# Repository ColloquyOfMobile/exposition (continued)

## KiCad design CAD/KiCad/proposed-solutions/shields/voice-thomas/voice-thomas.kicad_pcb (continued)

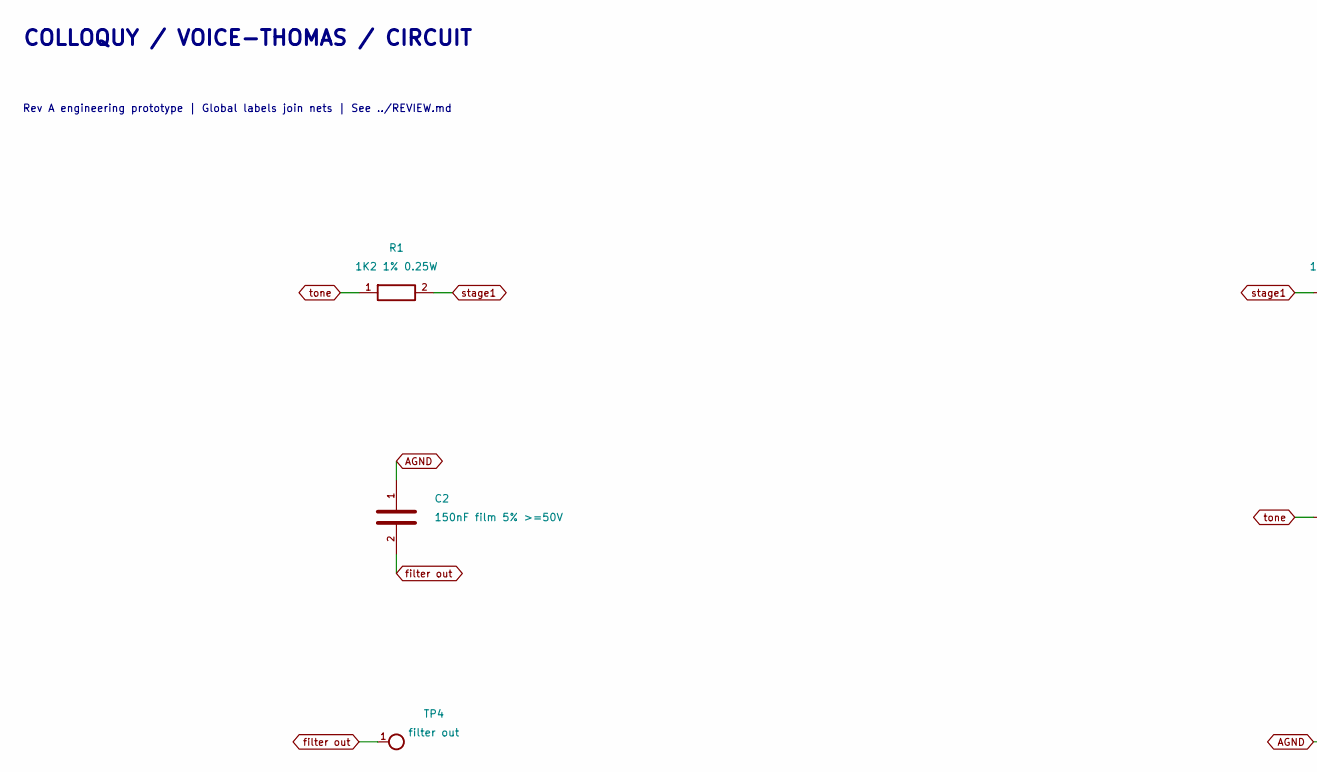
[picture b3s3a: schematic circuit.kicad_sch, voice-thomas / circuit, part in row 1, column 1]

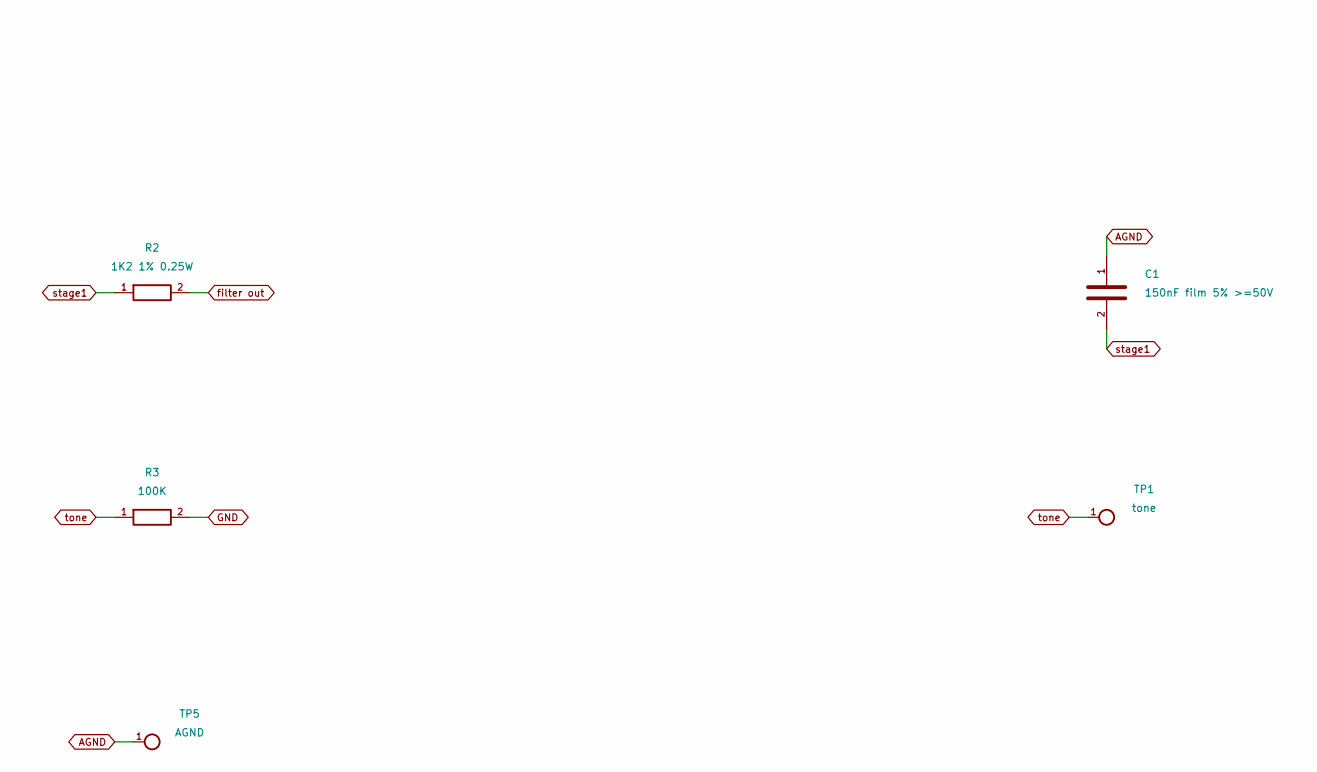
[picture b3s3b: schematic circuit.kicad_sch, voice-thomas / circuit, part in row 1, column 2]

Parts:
C1, C2: 150nF film 5% >=50V; C_Rect_L7.0mm_W6.5mm_P5.00mm
R1, R2: 1K2 1% 0.25W; R_Axial_DIN0207_L6.3mm_D2.5mm_P7.62mm_Horizontal
R3: 100K; R_Axial_DIN0207_L6.3mm_D2.5mm_P7.62mm_Horizontal
TP1: tone; TestPoint_Pad_D1.5mm
TP4: filter out; TestPin_1x01_P2.54mm
TP5: AGND; TestPin_1x01_P2.54mm

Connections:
AGND: C1.1, C2.1, TP5.1; also elsewhere on the board
GND: R3.2; also elsewhere on the board
filter out: C2.2, R2.2, TP4.1; also elsewhere on the board
stage1: C1.2, R1.2, R2.1
tone: R1.1, R3.1, TP1.1; also elsewhere on the board

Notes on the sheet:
COLLOQUY / VOICE-THOMAS / CIRCUIT
Rev A engineering prototype | Global labels join nets | See ../REVIEW.md

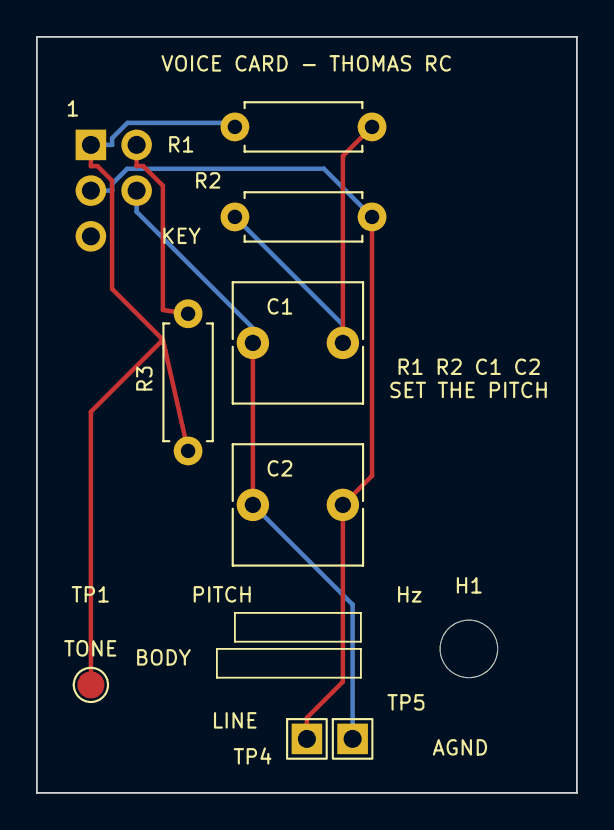
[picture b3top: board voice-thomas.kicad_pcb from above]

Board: 2 copper layers, 30.0 x 42.0 mm, 10 parts (1 on the bottom side), 5 nets.

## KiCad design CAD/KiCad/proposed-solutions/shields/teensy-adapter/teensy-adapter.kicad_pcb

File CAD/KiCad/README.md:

# Electronics: designs, references and production

Use these four folders to distinguish the files' purpose:

| Folder | Contents |
| --- | --- |
| [proposed-solutions](proposed-solutions/) | Editable replacement designs, including selected boards and alternative designs. |
| [old-reference](old-reference/) | Original installation boards, superseded designs and historical exports. |
| [provided-elements](provided-elements/) | Reference models and footprints of purchased/provided modules and component datasheets. |
| [production](production/) | Current checked fabrication, JLCPCB assembly files, schematic SVGs and 45° PCB previews. |

The authoritative manufacture selection is `export_gerbers.py` at the repository root;
`production/manifest.json` records its exact source files and hashes. The server reads
this selection and refuses stale packages. Alternative designs are not manufacturing orders.

| Manufacture | Quantity |
| --- | ---: |
| Shields backplane | 1 |
| Teensy 4.1 adapter | 1 |
| Voice Thomas card | 5 |
| Analyser carrier | 1 |
| **Microphone flex holder, Rev C (32 × 62 mm)** | **6** |
| Female base v2 | 3 |
| Male static v2 | 2 |

The Rev B microphone holder is historical. Manufacture the Rev C **microphone-flex**
board with removable JP1/JP2 selectors and three alternative module orientations.
Fit one MAX9814 module per holder; see its README for initial selector settings and fit checks.

Order packages are under `production/assembly/<board>/`; the combined download is
`production/assembly/colloquy-production.zip`. Each board package contains `gerbers.zip`,
`BOM.csv` with exact manufacturer/LCSC identification, `CPL.csv`, and manual/DNP instructions.
The analyser carrier has no SMD population and is assembled by hand.

Regenerate from the repository root using KiCad's Python: `python export_jlcpcb.py`.
This checks DRC, produces the assembly packages, and refreshes browser assets.

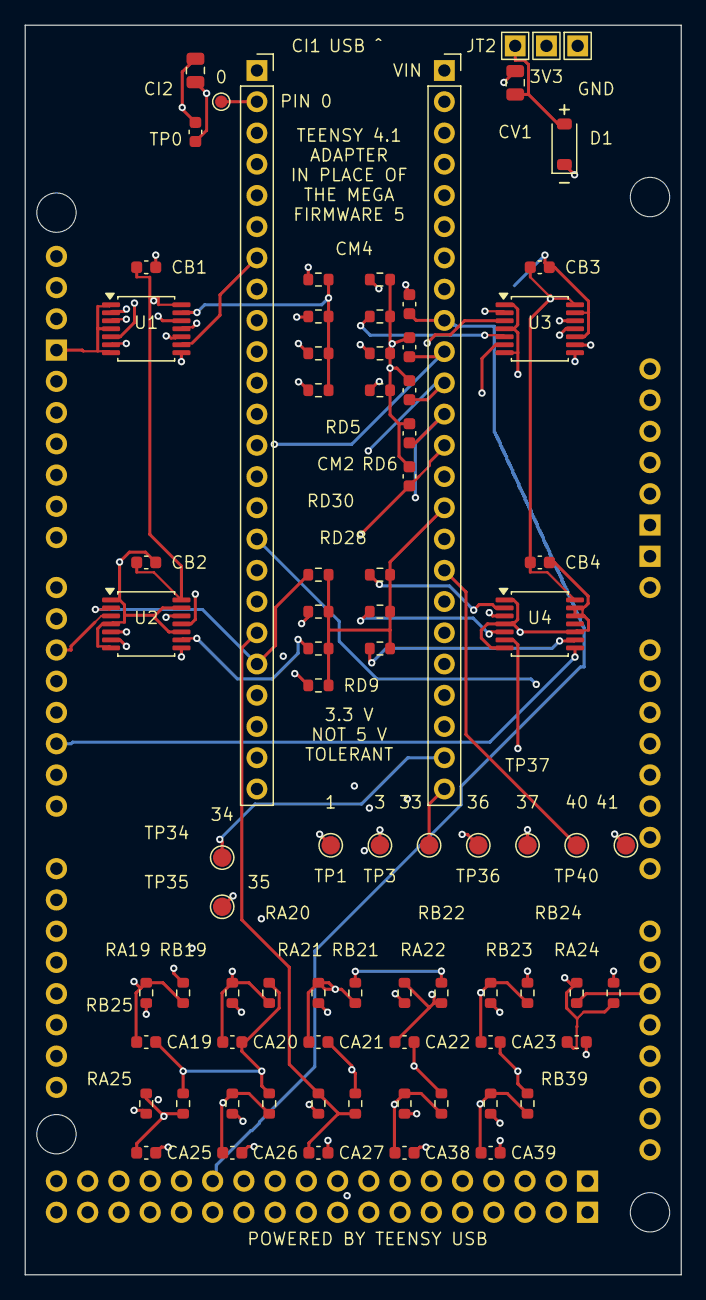
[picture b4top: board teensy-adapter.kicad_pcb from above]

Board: 4 copper layers, 53.3 x 101.6 mm, 85 parts (1 on the bottom side), 71 nets.

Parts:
CA19, CA20, CA21, CA22, CA23, CA24, CA25, CA26, CA27, CA38, CA39: 10nF C0G; C_0603_1608Metric
CB1, CB2, CB3, CB4: 100nF; C_0603_1608Metric
CI1: 10uF X7R; C_0805_2012Metric
CI2: 100nF; C_0603_1608Metric
CM1, CM2, CM3, CM4, CM5: 1nF C0G; C_0603_1608Metric
CV1: 10uF X7R; C_0805_2012Metric
D1: 1N5819HW; D_SOD-123
HM1, HM2, HM3, HM4: M3 computing shield; MountingHole_3.2mm_M3
JM1: MEGA PATTERN FEMALE; Mega_Female
JT1: Teensy 4.1 JT1; PinSocket_1x24_P2.54mm_Vertical
JT2: Teensy 4.1 JT2; PinSocket_1x24_P2.54mm_Vertical
RA19, RA20, RA21, RA22, RA23, RA24, RA25, RA26, RA27, RA38, RA39: 100K; R_0603_1608Metric
RB19, RB20, RB21, RB22, RB23, RB24, RB25, RB26, RB27, RB38, RB39: 150K; R_0603_1608Metric
RD2, RD4, RD5, RD6, RD7, RD8, RD9, RD10, RD11, RD12, RD28, RD29, RD30, RD31, RD32: 100K; R_0603_1608Metric
TP0: gpio/0; TestPoint_Pad_D1.0mm
TP1: gpio/1; TestPoint_Pad_D1.5mm
TP3: gpio/3; TestPoint_Pad_D1.5mm
TP33: gpio/33; TestPoint_Pad_D1.5mm
TP34: gpio/34; TestPoint_Pad_D1.5mm
TP35: gpio/35; TestPoint_Pad_D1.5mm
TP36: gpio/36; TestPoint_Pad_D1.5mm
TP37: gpio/37; TestPoint_Pad_D1.5mm
TP40: gpio/40; TestPoint_Pad_D1.5mm
TP41: gpio/41; TestPoint_Pad_D1.5mm
TPG: GND; TestPin_1x01_P2.54mm
TPI: IOREF; TestPin_1x01_P2.54mm
TPV: VIN_USB; TestPin_1x01_P2.54mm
U1, U2, U3, U4: SN74LV4T125PWR; TSSOP-14_4.4x5mm_P0.65mm

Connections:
GND: CA19.2, CA20.2, CA21.2, CA22.2, CA23.2, CA24.2, CA25.2, CA26.2, CA27.2, CA38.2, CA39.2, CB1.2, CB2.2, CB3.2, CB4.2, CI1.2, CI2.2, CM1.2, CM2.2, CM3.2, CM4.2, CM5.2, CV1.2, JM1.GND1, JM1.GND2, JM1.GND3, JM1.GND5, JM1.GND6, JT1.1, JT2.2, JT2.15, RB19.2, RB20.2, RB21.2, RB22.2, RB23.2, RB24.2, RB25.2, RB26.2, RB27.2, RB38.2, RB39.2, RD2.2, RD4.2, RD5.2, RD6.2, RD7.2, RD8.2, RD9.2, RD10.2, RD11.2, RD12.2, RD28.2, RD29.2, RD30.2, RD31.2, RD32.2, TPG.1, U1.1, U1.4, U1.7, U1.10, U1.13, U2.1, U2.4, U2.7, U2.10, U2.13, U3.1, U3.4, U3.7, U3.10, U3.13, U4.1, U4.4, U4.7, U4.10, U4.12, U4.13
IOREF: CI1.1, CI2.1, JT1.15, JT2.3, TPI.1
MEGA_5V: D1.1, JM1.5V1, JM1.5V3, JM1.5V4
VIN_USB: CB1.1, CB2.1, CB3.1, CB4.1, CV1.1, D1.2, JT2.1, TPV.1, U1.14, U2.14, U3.14, U4.14
adc/19: CA19.1, JT2.8, RA19.2, RB19.1
adc/20: CA20.1, JT2.7, RA20.2, RB20.1
adc/21: CA21.1, JT2.6, RA21.2, RB21.1
adc/22: CA22.1, JT2.5, RA22.2, RB22.1
adc/23: CA23.1, JT2.4, RA23.2, RB23.1
adc/24: CA24.1, JT1.16, RA24.2, RB24.1
adc/25: CA25.1, JT1.17, RA25.2, RB25.1
adc/26: CA26.1, JT1.18, RA26.2, RB26.1
adc/27: CA27.1, JT1.19, RA27.2, RB27.1
adc/38: CA38.1, JT2.19, RA38.2, RB38.1
adc/39: CA39.1, JT2.18, RA39.2, RB39.1
amp shutdown: JM1.D2, U4.8
female1/mic direct: CM1.1, JM1.D26, JT2.13
female1/neopixel/driven: JM1.D14, U2.6
female1/photosensor: JM1.A5, RA19.1
female1/tone: JM1.D6, U1.3
female2/mic direct: CM2.1, JM1.D27, JT2.12
female2/neopixel/driven: JM1.D7, U2.8
female2/photosensor: JM1.A6, RA20.1
female2/tone: JM1.D46, U1.6
female3/mic direct: CM3.1, JM1.D28, JT2.11
female3/neopixel/driven: JM1.D8, U2.11
female3/photosensor: JM1.A7, RA21.1
female3/tone: JM1.D10, U1.8
gpio/0: JT1.2, TP0.1
gpio/1: JT1.3, TP1.1
gpio/2: JT1.4, RD2.1, U1.2
gpio/3: JT1.5, TP3.1
gpio/4: JT1.6, RD4.1, U1.5
gpio/5: JT1.7, RD5.1, U1.9
gpio/6: JT1.8, RD6.1, U1.12
gpio/7: JT1.9, RD7.1, U2.5
gpio/8: JT1.10, RD8.1, U2.9
gpio/9: JT1.11, RD9.1, U2.12
gpio/10: JT1.12, RD10.1, U3.2
gpio/11: JT1.13, RD11.1, U3.5
gpio/12: JT1.14, RD12.1, U3.9
gpio/28: JT1.20, RD28.1, U2.2
gpio/29: JT1.21, RD29.1, U3.12
gpio/30: JT1.22, RD30.1, U4.2
gpio/31: JT1.23, RD31.1, U4.5
gpio/32: JT1.24, RD32.1, U4.9
gpio/33: JT2.24, TP33.1
gpio/34: JT2.23, TP34.1
gpio/35: JT2.22, TP35.1
gpio/36: JT2.21, TP36.1
gpio/37: JT2.20, TP37.1
gpio/40: JT2.17, TP40.1
gpio/41: JT2.16, TP41.1
male1/aux driven: JM1.D24, U4.3
male1/bar neopixel/driven: JM1.D16, U3.11
male1/mic direct: CM4.1, JM1.D29, JT2.10
male1/neopixel/driven: JM1.D9, U3.3
male1/photosensor/A: JM1.A8, RA22.1
male1/photosensor/B: JM1.A9, RA23.1
male1/photosensor/C: JM1.A10, RA24.1
male1/photosensor/D: JM1.A11, RA25.1
male1/tone: JM1.D11, U1.11
male2/aux driven: JM1.D25, U4.6
male2/bar neopixel/driven: JM1.D17, U3.8
male2/mic direct: CM5.1, JM1.D30, JT2.9
male2/neopixel/driven: JM1.D15, U3.6
male2/photosensor/A: JM1.A12, RA26.1
male2/photosensor/B: JM1.A13, RA27.1
male2/photosensor/C: JM1.A14, RA38.1
male2/photosensor/D: JM1.A15, RA39.1
male2/tone: JM1.D5, U2.3

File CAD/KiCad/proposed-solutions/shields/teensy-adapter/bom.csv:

Reference,Value,Footprint,MPN,Assembly
JM1,MEGA PATTERN FEMALE,Shields:Mega_Female,,fit
CM1,1nF C0G,Shields:C_0603_1608Metric,,fit
CM2,1nF C0G,Shields:C_0603_1608Metric,,fit
CM3,1nF C0G,Shields:C_0603_1608Metric,,fit
CM4,1nF C0G,Shields:C_0603_1608Metric,,fit
CM5,1nF C0G,Shields:C_0603_1608Metric,,fit
JT1,Teensy 4.1 JT1,Shields:PinSocket_1x24_P2.54mm_Vertical,,fit
JT2,Teensy 4.1 JT2,Shields:PinSocket_1x24_P2.54mm_Vertical,,fit
RD2,100K,Shields:R_0603_1608Metric,,fit
RD4,100K,Shields:R_0603_1608Metric,,fit
RD5,100K,Shields:R_0603_1608Metric,,fit
RD6,100K,Shields:R_0603_1608Metric,,fit
U1,SN74LV4T125PWR,Shields:TSSOP-14_4.4x5mm_P0.65mm,SN74LV4T125PWR,fit
CB1,100nF,Shields:C_0603_1608Metric,,fit
RD28,100K,Shields:R_0603_1608Metric,,fit
RD7,100K,Shields:R_0603_1608Metric,,fit
RD8,100K,Shields:R_0603_1608Metric,,fit
RD9,100K,Shields:R_0603_1608Metric,,fit
U2,SN74LV4T125PWR,Shields:TSSOP-14_4.4x5mm_P0.65mm,SN74LV4T125PWR,fit
CB2,100nF,Shields:C_0603_1608Metric,,fit
RD10,100K,Shields:R_0603_1608Metric,,fit
RD11,100K,Shields:R_0603_1608Metric,,fit
RD12,100K,Shields:R_0603_1608Metric,,fit
RD29,100K,Shields:R_0603_1608Metric,,fit
U3,SN74LV4T125PWR,Shields:TSSOP-14_4.4x5mm_P0.65mm,SN74LV4T125PWR,fit
CB3,100nF,Shields:C_0603_1608Metric,,fit
RD30,100K,Shields:R_0603_1608Metric,,fit
RD31,100K,Shields:R_0603_1608Metric,,fit
RD32,100K,Shields:R_0603_1608Metric,,fit
U4,SN74LV4T125PWR,Shields:TSSOP-14_4.4x5mm_P0.65mm,SN74LV4T125PWR,fit
CB4,100nF,Shields:C_0603_1608Metric,,fit
RA19,100K,Shields:R_0603_1608Metric,,fit
RB19,150K,Shields:R_0603_1608Metric,,fit
CA19,10nF C0G,Shields:C_0603_1608Metric,,fit
RA20,100K,Shields:R_0603_1608Metric,,fit
RB20,150K,Shields:R_0603_1608Metric,,fit
CA20,10nF C0G,Shields:C_0603_1608Metric,,fit
RA21,100K,Shields:R_0603_1608Metric,,fit
RB21,150K,Shields:R_0603_1608Metric,,fit
CA21,10nF C0G,Shields:C_0603_1608Metric,,fit
RA22,100K,Shields:R_0603_1608Metric,,fit
RB22,150K,Shields:R_0603_1608Metric,,fit
CA22,10nF C0G,Shields:C_0603_1608Metric,,fit
RA23,100K,Shields:R_0603_1608Metric,,fit
RB23,150K,Shields:R_0603_1608Metric,,fit
CA23,10nF C0G,Shields:C_0603_1608Metric,,fit
RA24,100K,Shields:R_0603_1608Metric,,fit
RB24,150K,Shields:R_0603_1608Metric,,fit
CA24,10nF C0G,Shields:C_0603_1608Metric,,fit
RA25,100K,Shields:R_0603_1608Metric,,fit
RB25,150K,Shields:R_0603_1608Metric,,fit
CA25,10nF C0G,Shields:C_0603_1608Metric,,fit
RA26,100K,Shields:R_0603_1608Metric,,fit
RB26,150K,Shields:R_0603_1608Metric,,fit
CA26,10nF C0G,Shields:C_0603_1608Metric,,fit
RA27,100K,Shields:R_0603_1608Metric,,fit
RB27,150K,Shields:R_0603_1608Metric,,fit
CA27,10nF C0G,Shields:C_0603_1608Metric,,fit
RA38,100K,Shields:R_0603_1608Metric,,fit
RB38,150K,Shields:R_0603_1608Metric,,fit
CA38,10nF C0G,Shields:C_0603_1608Metric,,fit
RA39,100K,Shields:R_0603_1608Metric,,fit
RB39,150K,Shields:R_0603_1608Metric,,fit
CA39,10nF C0G,Shields:C_0603_1608Metric,,fit
D1,1N5819HW,Shields:D_SOD-123,1N5819HW,fit
CV1,10uF X7R,Shields:C_0805_2012Metric,,fit
CI1,10uF X7R,Shields:C_0805_2012Metric,,fit
CI2,100nF,Shields:C_0603_1608Metric,,fit
TPV,VIN_USB,Shields:TestPin_1x01_P2.54mm,,fit
TPI,IOREF,Shields:TestPin_1x01_P2.54mm,,fit
TPG,GND,Shields:TestPin_1x01_P2.54mm,,fit

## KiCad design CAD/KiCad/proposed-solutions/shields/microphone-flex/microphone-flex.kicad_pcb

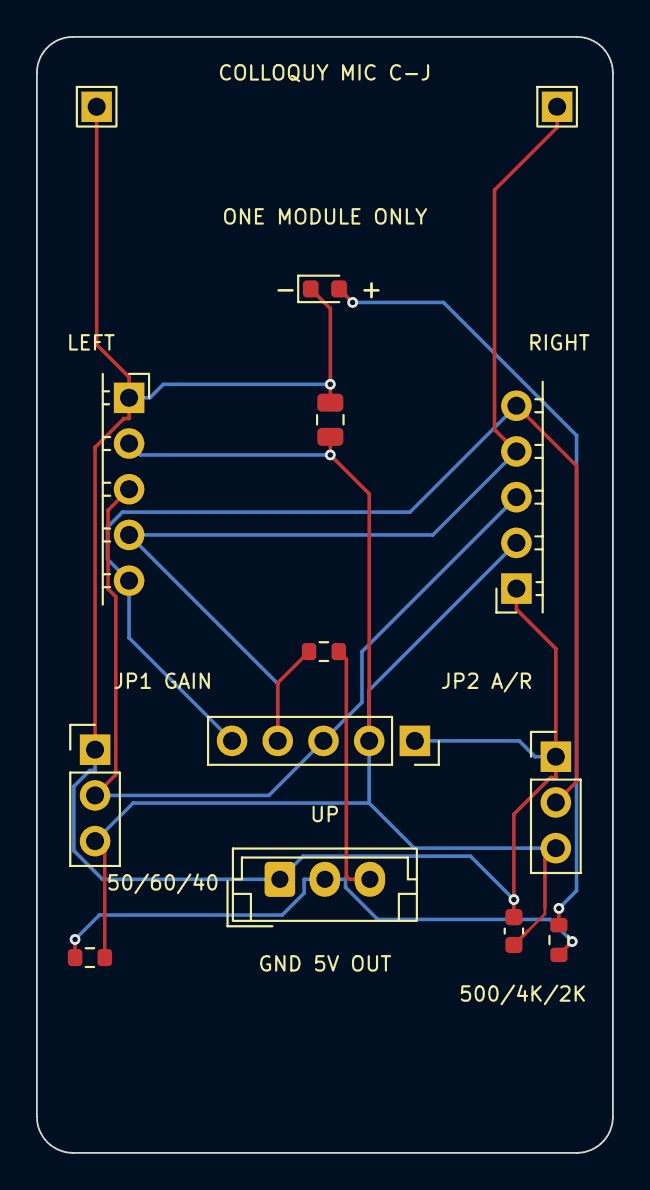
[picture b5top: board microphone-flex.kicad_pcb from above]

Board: 2 copper layers, 32.0 x 62.0 mm, 16 parts (0 on the bottom side), 8 nets.

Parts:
C6: 100nF; C_0603_1608Metric
C7: 22uF X5R 10V; C_0805_2012Metric
D1: GREEN LED; LED_0603_1608Metric
H1, H2: M5 SLOT 12x5.5 / TRANSVERSE; Flex_M5_Slot12x5.5_Keepout
J1: GND / +5V / OUT; JST_EH_B3B-EH-A_1x03_P2.50mm_Vertical
J2: LEFT / DOWNWARD MODULE; Flex_Socket_Left_Overhang
J3: RIGHT / DOWNWARD MODULE; Flex_Socket_Right_Overhang
JP1: GAIN SELECT / HEADER + SHUNT; Flex_Gain_Selector
JP2: AR SELECT / HEADER + SHUNT; Flex_AR_Selector
M1: UP / ONE MODULE ONLY; Flex_Socket_Up
R4: 33R; R_0603_1608Metric
R5: 470R; R_0603_1608Metric
R6: 2K2; R_0603_1608Metric
TP1: MICOUT; TestPin_1x01_P2.54mm
TP2: GND; TestPin_1x01_P2.54mm

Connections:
+5V: J1.2, R4.1, R6.1
AR: J2.5, J3.5, JP2.2, M1.5
GAIN: J2.3, J3.3, JP1.2, M1.3
GND: C6.2, C7.2, D1.1, J1.1, J2.1, J3.1, JP1.1, JP2.1, M1.1, TP2.1
MICOUT: J2.4, J3.4, M1.4, R5.1, TP1.1
OUT: J1.3, R5.2
VDD: C6.1, C7.1, J2.2, J3.2, JP1.3, JP2.3, M1.2, R4.2
led/D1: D1.2, R6.2

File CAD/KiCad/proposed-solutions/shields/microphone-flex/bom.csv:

Reference,Value,Footprint,MPN,Assembly
M1,UP / ONE MODULE ONLY,Shields:Flex_Socket_Up,Existing MAX9814 module + 1x05 2.54mm female socket,fit
R4,33R,Shields:R_0603_1608Metric,,fit
C7,22uF X5R 10V,Shields:C_0805_2012Metric,,fit
C6,100nF,Shields:C_0603_1608Metric,,fit
R6,2K2,Shields:R_0603_1608Metric,,fit
D1,GREEN LED,Shields:LED_0603_1608Metric,,fit
R5,470R,Shields:R_0603_1608Metric,,fit
J1,GND / +5V / OUT,Shields:JST_EH_B3B-EH-A_1x03_P2.50mm_Vertical,B3B-EH-A,fit
TP1,MICOUT,Shields:TestPin_1x01_P2.54mm,,fit
TP2,GND,Shields:TestPin_1x01_P2.54mm,,fit
JP1,GAIN SELECT / HEADER + SHUNT,Shields:Flex_Gain_Selector,Gold plated 1x03 2.54mm vertical header + removable 1x02 shunt,fit
JP2,AR SELECT / HEADER + SHUNT,Shields:Flex_AR_Selector,Gold plated 1x03 2.54mm vertical header + removable 1x02 shunt,fit
J2,LEFT / DOWNWARD MODULE,Shields:Flex_Socket_Left_Overhang,1x05 P2.54mm horizontal female socket; verify purchased dimensions,fit
J3,RIGHT / DOWNWARD MODULE,Shields:Flex_Socket_Right_Overhang,1x05 P2.54mm horizontal female socket; verify purchased dimensions,fit

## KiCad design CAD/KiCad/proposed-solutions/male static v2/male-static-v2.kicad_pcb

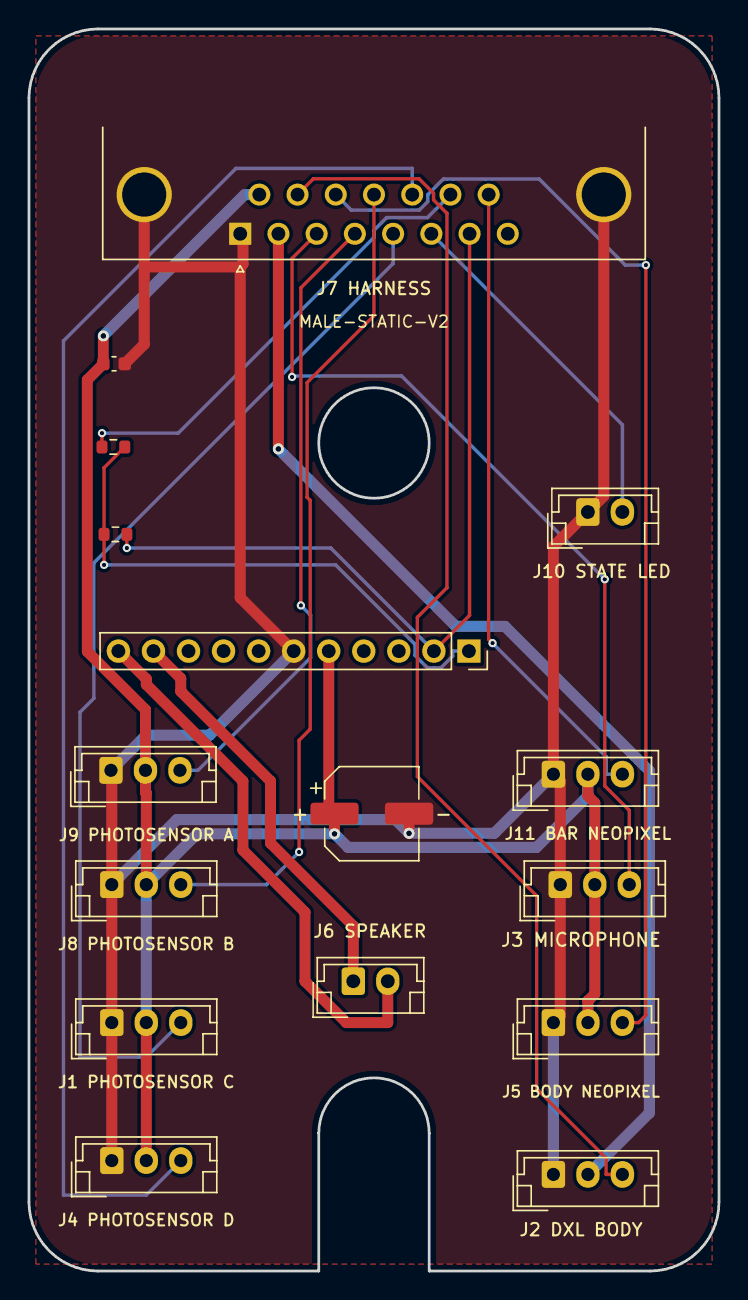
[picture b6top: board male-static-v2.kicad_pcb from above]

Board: 2 copper layers, 50.0 x 90.0 mm, 16 parts (0 on the bottom side), 17 nets.

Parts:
C1: 220uF 10V / provisional; CP_Elec_6.3x5.8
C2: 100nF; C_0603_1608Metric
J1: photosensor; J1_original
J2: dxl male; J2_original
J3: microphone; J3_original
J4: photosensor; J4_original
J5: body neopixel; J5_original
J6: Speaker; J6_original
J7: DA15_Plug_MountingHoles; J7_original
J8: photosensor; J8_original
J9: photosensor; J9_original
J10: State LED; J10_original
J11: bar neopixel; J11_original
M1: GF1002 / 1x11 female socket; GF1002_PlugIn_1x11
R1: 22K; R_0603_1608Metric
R2: 3K3; R_0603_1608Metric

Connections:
5V: C1.1, C2.1, J1.2, J3.2, J4.2, J5.2, J7.9, J8.2, J9.2, J11.2, M1.5
12V: J2.2, J7.2
AMP_INPUT: M1.1, R1.2, R2.1
AMP_OUT_N: J6.2, M1.11
AMP_OUT_P: J6.1, M1.10
AUDIO_RETURN: J7.7, M1.2, R2.2
GND: C1.2, C2.2, J1.1, J2.1, J3.1, J4.1, J5.1, J7.0, J7.1, J8.1, J9.1, J10.1, J11.1, M1.6
LINE_IN: J7.14, R1.1
bar neopixel male input: J7.15, J11.3
body neopixel male input: J5.3, J7.11
dynamixel data: J2.3, J7.10
microphone male output: J3.3, J7.3
photo sensor male output a: J7.4, J9.3
photo sensor male output b: J7.12, J8.3
photo sensor male output c: J1.3, J7.5
photo sensor male output d: J4.3, J7.13
state LED male output: J7.6, J10.2

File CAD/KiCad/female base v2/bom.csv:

Reference,Value,Footprint,Description
J4,photosensor,Body:J4_original,Original harness pin order retained. J6 now carries the local amplifier output.
J2,dxl mirror,Body:J2_original,Original harness pin order retained. J6 now carries the local amplifier output.
J7,DA15_Plug_MountingHoles,Body:J7_original,Original harness pin order retained. J6 now carries the local amplifier output.
J3,microphone,Body:J3_original,Original harness pin order retained. J6 now carries the local amplifier output.
J5,neopixel,Body:J5_original,Original harness pin order retained. J6 now carries the local amplifier output.
J6,Speaker,Body:J6_original,Original harness pin order retained. J6 now carries the local amplifier output.
R1,22K,Resistor_SMD:R_0603_1608Metric,
R2,3K3,Resistor_SMD:R_0603_1608Metric,
C1,220uF 10V / provisional,Capacitor_THT:CP_Radial_D6.3mm_P2.50mm,Provisional local reservoir; verify actual amplifier transients and rail sag before release.
C2,100nF,Capacitor_SMD:C_0603_1608Metric,
M1,GF1002 / 1x11 female socket,Body:GF1002_PlugIn_1x11,"Plug-in module: 1x3, 1x2 and 1x4 downward male headers in an 11-pin female socket. Nominal underside gap 11mm. Pin 10=ROUT+, 11=ROUT- is provisional: verify module polarity before ordering."

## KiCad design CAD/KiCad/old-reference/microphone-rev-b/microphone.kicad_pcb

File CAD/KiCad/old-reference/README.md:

# Historical references — do not order

Original installation PCBs, original supplied board archives, superseded shield designs,
the old Rev B microphone holder, and superseded production exports are retained here.
Their old Gerbers and manufacturing ZIPs are historical records.

Use [the current production selection](../README.md) for all new orders.

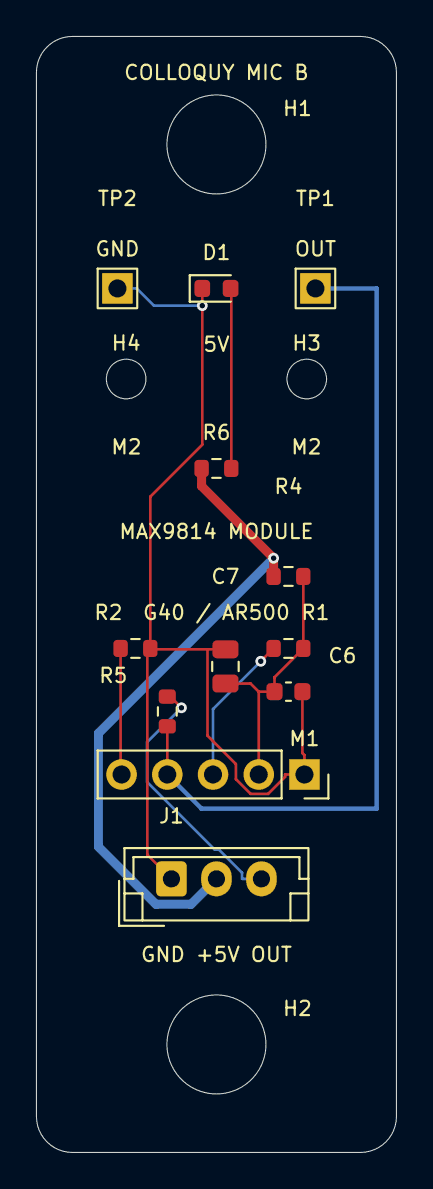
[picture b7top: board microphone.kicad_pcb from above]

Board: 2 copper layers, 20.0 x 62.0 mm, 16 parts (0 on the bottom side), 8 nets.

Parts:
C6: 100nF; C_0603_1608Metric
C7: 22uF X5R 10V; C_0805_2012Metric
D1: GREEN LED; LED_0603_1608Metric
H1, H2: M5 / 12mm copper keepout; MountingHole_5.5mm_Keepout12
H3, H4: M2 MODULE / INSULATING SPACER; MountingHole_2.2mm_M2_Keepout6
J1: GND / +5V / OUT; JST_EH_B3B-EH-A_1x03_P2.50mm_Vertical
M1: MAX9814 MODULE / 1x05 SOCKET; MAX9814_Module_Socket_1x05
R1: 0R / GAIN VDD 40dB; R_0603_1608Metric
R2: 0R / AR GND 1:500; R_0603_1608Metric
R4: 33R; R_0603_1608Metric
R5: 470R; R_0603_1608Metric
R6: 2K2; R_0603_1608Metric
TP1: MICOUT; TestPin_1x01_P2.54mm
TP2: GND; TestPin_1x01_P2.54mm

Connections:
+5V: J1.2, R4.1, R6.1
AR: M1.5, R2.1
GAIN: M1.3, R1.1
GND: C6.2, C7.2, D1.1, J1.1, M1.1, R2.2, TP2.1
MICOUT: M1.4, R5.1, TP1.1
OUT: J1.3, R5.2
VDD: C6.1, C7.1, M1.2, R1.2, R4.2
led/D1: D1.2, R6.2
